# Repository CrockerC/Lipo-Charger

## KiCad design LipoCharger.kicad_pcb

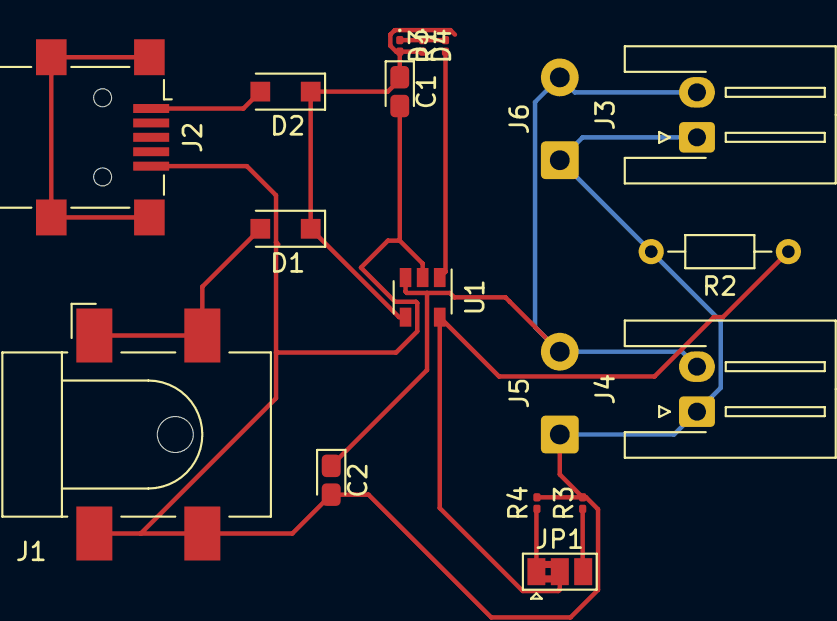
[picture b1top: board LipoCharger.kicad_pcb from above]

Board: 2 copper layers, 18 parts (0 on the bottom side), 10 nets.

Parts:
C1: 1.7uF; CP_EIA-1608-08_AVX-J_Pad1.25x1.05mm_HandSolder
C2: 4.7uF; CP_EIA-1608-08_AVX-J_Pad1.25x1.05mm_HandSolder
D1, D2: MBRA140; D_SOD-123F
D3: DNP; LED_0201_0603Metric
D4: RED; LED_0201_0603Metric
J1: POWER_JACKSMD; BarrelJack_CLIFF_FC681465S_SMT_Horizontal
J2: USB_B_Micro; USB_Mini-B_Lumberg_2486_01_Horizontal
J3, J4: Conn_01x02_Female; JST_XH_S2B-XH-A-1_1x02_P2.50mm_Horizontal
J5, J6: Conn_01x02; SolderWire-0.5sqmm_1x02_P4.6mm_D0.9mm_OD2.1mm
JP1: SolderJumper_3_Bridged12; SolderJumper-3_P1.3mm_Bridged2Bar12_Pad1.0x1.5mm
R1: 330; R_0201_0603Metric
R2: PROG; R_Axial_DIN0204_L3.6mm_D1.6mm_P7.62mm_Horizontal
R3: 10k; R_0201_0603Metric
R4: 2k; R_0201_0603Metric
U1: MCP73831-2-OT; SOT-23-5

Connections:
Earth: C1.2, C2.2, J1.2, J1.3, J2.5, J3.1, J4.1, J5.1, J6.1, R2.2, R3.2, R4.2, U1.2
unnamed: C1.1, D1.1, D2.1, D3.2, D4.2, U1.4
unnamed: C2.1, J3.2, J4.2, J5.2, J6.2, U1.3
unnamed: D1.2, J1.1
unnamed: D2.2, J2.1
unnamed: D3.1, D4.1, R1.2
unnamed: JP1.1, R4.1
unnamed: JP1.2, R2.1, U1.5
unnamed: JP1.3, R3.1
unnamed: R1.1, U1.1
